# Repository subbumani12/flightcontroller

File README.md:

# Flight Controller

A custom **STM32F411-based flight controller PCB** designed for multirotor, UAV, robotics, and embedded flight-control applications.

The board integrates an IMU, magnetometer, barometric sensor, EEPROM, MicroSD storage, USB-C, SWD debugging, UART interfaces, and dedicated motor/auxiliary outputs on a compact **2-layer PCB** designed in KiCad.

## 3D Render

---

## ✈️ Overview

This project is a custom flight-controller hardware design centered around the **STM32F411RET6 ARM Cortex-M4** microcontroller.

The STM32 handles sensor acquisition, flight-control processing, peripheral communication, data logging, and motor/auxiliary output generation.

The board combines:

* Inertial sensing
* Magnetic heading measurement
* Barometric altitude measurement
* Non-volatile configuration storage
* Flight-data logging
* USB communication
* SWD programming/debugging
* Motor and auxiliary outputs
* UART communication

The PCB was designed in **KiCad**, with emphasis on compact routing, sensor decoupling, accessible debugging, and organized external interfaces.

---

## 🔧 Hardware Features

| Component             | Part                                              |
| --------------------- | ------------------------------------------------- |
| **Microcontroller**   | STM32F411RET6                                     |
| **IMU**               | LSM6DS3 – 3-axis Accelerometer + 3-axis Gyroscope |
| **Magnetometer**      | LIS3MDL – 3-axis                                  |
| **Barometer**         | BMP280                                            |
| **EEPROM**            | AT24C256A                                         |
| **Storage**           | MicroSD                                           |
| **USB**               | USB Type-C                                        |
| **Debug**             | SWD                                               |
| **Serial**            | UART1 / UART2                                     |
| **Motor Outputs**     | MOTOR1 / MOTOR2 / MOTOR3                          |
| **Auxiliary Outputs** | AUX1 / AUX2 / AUX3                                |
| **Logic Supply**      | 3.3 V                                             |
| **PCB**               | 2-layer                                           |
| **EDA Tool**          | KiCad                                             |

The complete hardware feature set is documented in the original design specification.

---

## 🧠 System Architecture

```text
                         USB Type-C
                             │
                             ▼
                       USB Protection
                             │
                             ▼
                       Power / 3.3 V
                             │
                             ▼
                    ┌─────────────────┐
                    │   STM32F411     │
                    │   Flight MCU    │
                    └────────┬────────┘
                             │
          ┌──────────────────┼──────────────────┐
          │                  │                  │
          ▼                  ▼                  ▼
        I²C                 SPI               UART
          │                  │                  │
    ┌─────┼─────┐       ┌────┴────┐       ┌────┴────┐
    ▼     ▼     ▼       ▼         ▼       ▼         ▼
  LSM6DS3 LIS3MDL EEPROM BMP280   MicroSD  UART1    UART2
    │     │
    └─────┴────── Sensor Data
                    │
                    ▼
              STM32 Processing
                    │
             ┌──────┴──────┐
             ▼             ▼
        Motor Outputs   AUX Outputs
             │
             ▼
            ESCs
```

---

## 📡 Sensors & Peripherals

### LSM6DS3 IMU

The **LSM6DS3** provides:

* 3-axis accelerometer
* 3-axis gyroscope

It serves as the primary inertial sensor for attitude estimation, angular-rate measurement, motion detection, and flight-control feedback.

The IMU communicates with the STM32 through **I²C**.

### LIS3MDL Magnetometer

The **LIS3MDL** provides 3-axis magnetic-field measurements and can be used as a magnetic heading reference for navigation and orientation estimation.

It communicates through **I²C** and includes an interrupt connection to the MCU.

### BMP280 Barometer

The **BMP280** provides pressure measurements for:

* Relative altitude estimation
* Altitude-hold applications
* Vertical-motion estimation
* Flight-data logging

The sensor is connected through **SPI**.

### AT24C256A EEPROM

The onboard EEPROM provides non-volatile storage for:

* Configuration parameters
* Calibration data
* Controller settings
* Persistent system information

### MicroSD

A dedicated MicroSD interface provides onboard flight-data storage using SPI:

```text
SD_SPI_MOSI
SD_SPI_MISO
SD_SPI_SCK
SD_CHIPSEL
```

It can be used for sensor measurements, telemetry, debugging information, controller parameters, and flight logs.

---

## 🔌 Interfaces

### Motor Outputs

Three dedicated motor interfaces are provided:

```text
MOTOR1_OUT
MOTOR2_OUT
MOTOR3_OUT
```

Each connector provides:

```text
+5V
GND
SIGNAL
```

The motor-control signals are generated using STM32 timer peripherals and can interface with external ESCs or motor-control hardware.

### Auxiliary Outputs

```text
AUX1_OUT
AUX2_OUT
AUX3_OUT
```

Each provides:

```text
+5V
GND
SIGNAL
```

These can be used for additional actuators or flight-controller peripherals.

### UART

Two serial interfaces are exposed:

```text
UART1_TX
UART1_RX

UART2_TX
UART2_RX
```

Potential applications include GPS, telemetry, radio receivers, external sensors, and configuration interfaces.

### SWD

A dedicated SWD interface is provided for programming and debugging:

```text
SWDIO
SWCLK
3.3V
GND
```

The board also includes test points for convenient hardware debugging.

---

## ⚡ Power Architecture

The board uses an onboard **3.3 V regulation stage** for the STM32 and peripheral electronics.

The power section includes:

* Schottky diode protection
* AMS1117-3.3 regulator
* Input/output filtering capacitors
* Power indicator LED
* Ferrite filtering for the MCU supply

The additional ferrite filtering is intended to reduce high-frequency supply noise around the MCU.

---

## 🖥️ USB & Debugging

The board includes a **USB Type-C interface** providing:

* USB D+
* USB D−
* VBUS
* GND

USB ESD protection is included on the data interface.

The USB connection can be used for firmware development, communication, configuration, debugging, and powering the board during development.

Dedicated **BOOT** and **RESET** buttons are also provided for firmware programming, recovery, and MCU reset.

---

## 🧩 PCB Design

Designed using **KiCad**, the PCB focuses on compact two-layer implementation and practical hardware debugging.

### Design considerations

* Compact 2-layer PCB
* Dedicated ground routing/plane
* Local sensor decoupling
* Short high-speed peripheral connections
* Compact MCU placement
* Accessible SWD interface
* Dedicated motor and auxiliary connectors
* UART connectors
* USB Type-C
* Ferrite-filtered MCU supply
* Separated sensitive sensor circuitry
* Hardware test points
* Perimeter mounting holes

---

## 🔄 Flight-Control Data Flow

```text
        ┌─────────────┐
        │    IMU      │
        │   LSM6DS3   │
        └──────┬──────┘
               │
        ┌──────▼──────┐
        │ Magnetometer│
        │   LIS3MDL   │
        └──────┬──────┘
               │
        ┌──────▼──────┐
        │  Barometer  │
        │    BMP280   │
        └──────┬──────┘
               │
               ▼
        ┌──────────────┐
        │  STM32F411   │
        │    MCU       │
        └──────┬───────┘
               │
        ┌──────┼──────────┐
        ▼      ▼          ▼
     Motors   AUX     Telemetry
        │
        ▼
       ESCs
```

The STM32 acquires sensor data, processes the measurements using flight-control firmware, and generates outputs for connected ESCs, motors, and auxiliary peripherals.

---

## 🛠️ Tools & Technologies

* **KiCad** – Schematic & PCB design
* **STM32F411RET6** – ARM Cortex-M4 MCU
* **STM32 development tools / STM32CubeIDE**
* **I²C**
* **SPI**
* **USART**
* **USB**
* **SWD**

---

## 🚀 Potential Future Improvements

Possible future revisions include:

* Additional motor channels
* CAN / CAN-FD
* GPS connector
* Dedicated telemetry interface
* Battery voltage/current monitoring
* Buzzer interface
* Additional IMU / redundant sensors
* External compass connector
* Barometer isolation
* Improved power-input protection
* Dedicated receiver interface
* Additional test points
* Improved PCB signal integrity

---

## 🎯 Applications

This hardware platform can be explored for:

* Multirotor flight controllers
* UAV development
* Drone flight-control systems
* Autonomous aerial vehicles
* Embedded navigation
* Sensor-fusion experiments
* Flight-data logging
* Robotics
* Embedded control systems
* UAV hardware prototyping

---

## 📌 Project Status

**Hardware:** PCB design completed
**EDA:** KiCad
**Architecture:** STM32F411-based
**PCB:** 2-layer

This project is intended for **educational, research, and UAV hardware-development purposes**.

---

## 📄 License

This project is open-source and intended for educational, research, and UAV hardware-development purposes.

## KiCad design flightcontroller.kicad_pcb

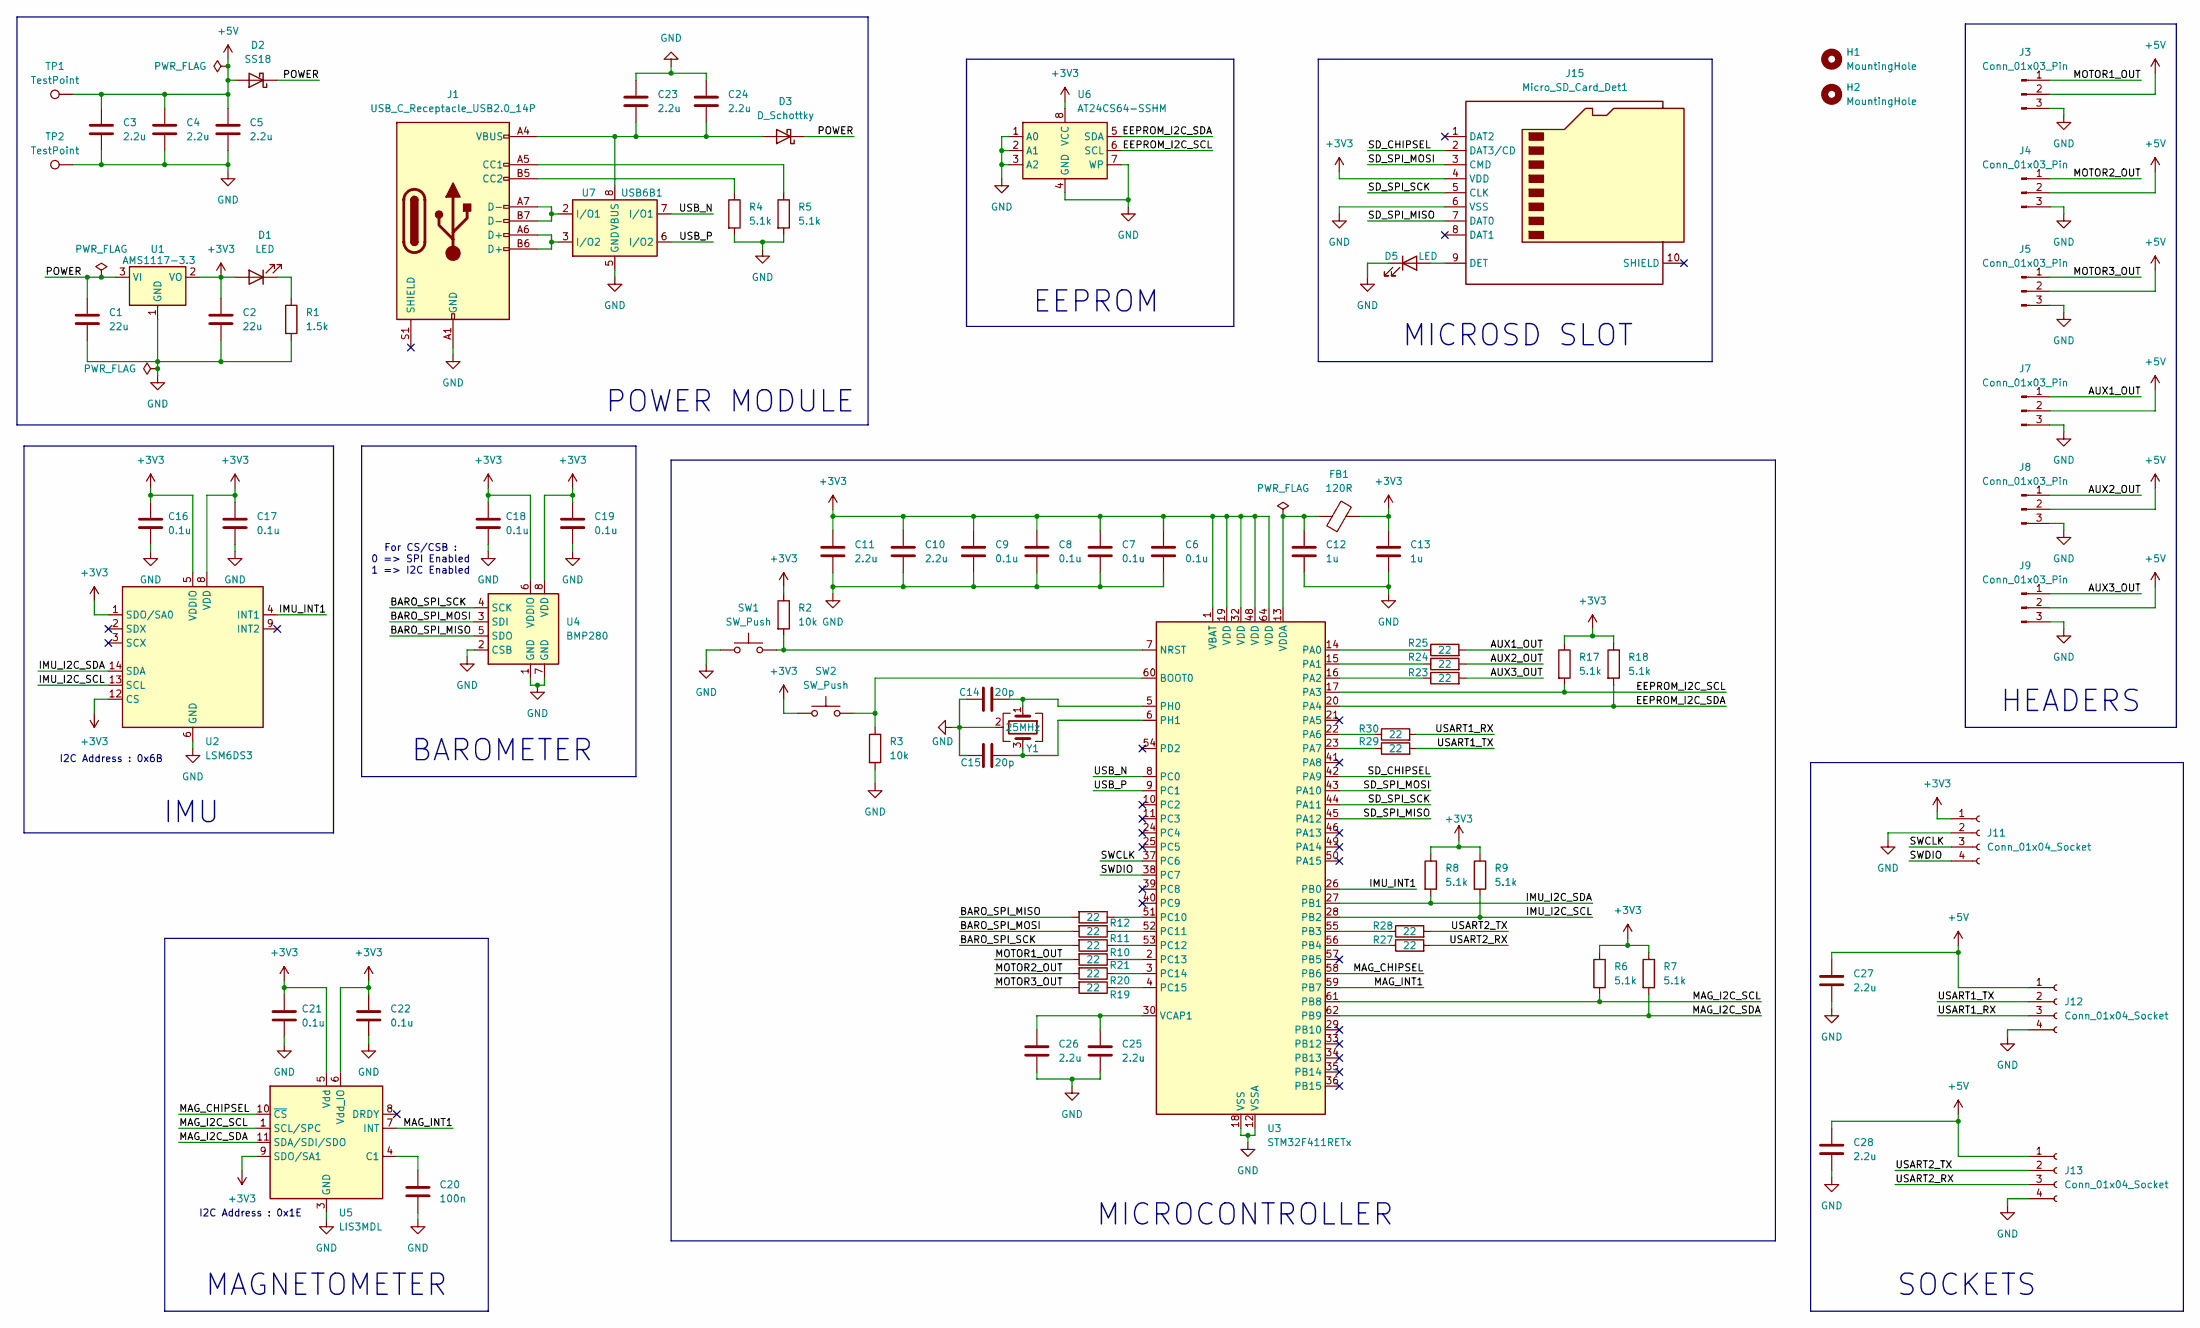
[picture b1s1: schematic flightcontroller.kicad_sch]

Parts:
C1, C2: 22u; C_0402_1005Metric
C3, C4, C5, C10, C11, C23, C24, C25, C26, C27, C28: 2.2u; C_0402_1005Metric
C6, C7, C8, C9, C16, C17, C18, C19, C21, C22: 0.1u; C_0402_1005Metric
C12, C13: 1u; C_0402_1005Metric
C14, C15: 20p; C_0402_1005Metric
C20: 100n; C_0402_1005Metric
D1, D5: LED; LED_0603_1608Metric
D2: SS18; D_SMA
D3: D_Schottky; D_0603_1608Metric
FB1: 120R; L_0805_2012Metric
H1, H2: MountingHole; MountingHole_5mm
J1: USB_C_Receptacle_USB2.0_14P; USB_C_Receptacle_HRO_TYPE-C-31-M-12
J3, J4, J5, J7, J8, J9: Conn_01x03_Pin; PinHeader_1x03_P2.54mm_Vertical
J11, J12, J13: Conn_01x04_Socket; PinSocket_1x04_P2.54mm_Vertical
J15: Micro_SD_Card_Det1; microSD_HC_Molex_104031-0811
R1: 1.5k; R_0402_1005Metric
R2, R3: 10k; R_0402_1005Metric
R4, R5, R6, R7, R8, R9, R17, R18: 5.1k; R_0402_1005Metric
R10, R11, R12, R19, R20, R21, R23, R24, R25, R27, R28, R29, R30: 22; R_0402_1005Metric
SW1, SW2: SW_Push; SW_SPST_TL3305A
TP1, TP2: TestPoint; TestPoint_THTPad_D2.0mm_Drill1.0mm
U1: AMS1117-3.3; SOT-223-3_TabPin2
U2: LSM6DS3; LGA-14_3x2.5mm_P0.5mm_LayoutBorder3x4y
U3: STM32F411RETx; LQFP-64_10x10mm_P0.5mm
U4: BMP280; Bosch_LGA-8_2x2.5mm_P0.65mm_ClockwisePinNumbering
U5: LIS3MDL; LGA-12_2x2mm_P0.5mm
U6: AT24CS64-SSHM; SOIC-8_3.9x4.9mm_P1.27mm
U7: USB6B1; SOIC-8_3.9x4.9mm_P1.27mm
Y1: 25MHz; Crystal_SMD_0603-4Pin_6.0x3.5mm

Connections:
+3V3: C2.1, C6.1, C7.1, C8.1, C9.1, C10.1, C11.1, C13.1, C16.1, C17.1, C18.1, C19.1, C21.1, C22.1, D1.2 (A), FB1.2, J11.1, J15.4 (VDD), R2.1, R6.1, R7.1, R8.1, R9.1, R17.1, R18.1, SW2.1, U1.2 (VO), U2.1 (SDO/SA0), U2.5 (VDDIO), U2.8 (VDD), U2.12 (CS), U3.1 (VBAT), U3.19 (VDD), U3.32 (VDD), U3.48 (VDD), U3.64 (VDD), U4.6 (VDDIO), U4.8 (VDD), U5.5 (Vdd), U5.6 (Vdd_IO), U5.9 (SDO/SA1), U6.8 (VCC)
+5V: C3.1, C4.1, C5.1, C27.1, C28.1, D2.2 (A), J3.2, J4.2, J5.2, J7.2, J8.2, J9.2, J12.1, J13.1, TP1.1
/AUX1_OUT: J7.1, R25.2
/AUX2_OUT: J8.1, R24.2
/AUX3_OUT: J9.1, R23.2
/BARO_SPI_MISO: R12.2, U4.5 (SDO)
/BARO_SPI_MOSI: R11.2, U4.3 (SDI)
/BARO_SPI_SCK: R10.2, U4.4 (SCK)
/EEPROM_I2C_SCL: R17.2, U3.17 (PA3), U6.6 (SCL)
/EEPROM_I2C_SDA: R18.2, U3.20 (PA4), U6.5 (SDA)
/IMU_I2C_SCL: R9.2, U2.13 (SCL), U3.28 (PB2)
/IMU_I2C_SDA: R8.2, U2.14 (SDA), U3.27 (PB1)
/IMU_INT1: U2.4 (INT1), U3.26 (PB0)
/MAG_CHIPSEL: U3.58 (PB6), U5.10 (~CS)
/MAG_I2C_SCL: R6.2, U3.61 (PB8), U5.1 (SCL/SPC)
/MAG_I2C_SDA: R7.2, U3.62 (PB9), U5.11 (SDA/SDI/SDO)
/MAG_INT1: U3.59 (PB7), U5.7 (INT)
/MOTOR1_OUT: J3.1, R21.2
/MOTOR2_OUT: J4.1, R20.2
/MOTOR3_OUT: J5.1, R19.2
/POWER: C1.1, D2.1 (K), D3.1 (K), U1.3 (VI)
/SD_CHIPSEL: J15.2 (DAT3/CD), U3.42 (PA9)
/SD_SPI_MISO: J15.7 (DAT0), U3.45 (PA12)
/SD_SPI_MOSI: J15.3 (CMD), U3.43 (PA10)
/SD_SPI_SCK: J15.5 (CLK), U3.44 (PA11)
/SWCLK: J11.3, U3.37 (PC6)
/SWDIO: J11.4, U3.38 (PC7)
/USART1_RX: J12.3, R30.2
/USART1_TX: J12.2, R29.2
/USART2_RX: J13.3, R27.2
/USART2_TX: J13.2, R28.2
/USB_N: U3.8 (PC0), U7.7 (I/O1)
/USB_P: U3.9 (PC1), U7.6 (I/O2)
GND: C1.2, C2.2, C3.2, C4.2, C5.2, C6.2, C7.2, C8.2, C9.2, C10.2, C11.2, C12.2, C13.2, C14.1, C15.2, C16.2, C17.2, C18.2, C19.2, C20.2, C21.2, C22.2, C23.1, C24.1, C25.2, C26.2, C27.2, C28.2, D5.1 (K), J1.A1 (GND), J1.A12 (GND), J1.B1 (GND), J1.B12 (GND), J3.3, J4.3, J5.3, J7.3, J8.3, J9.3, J11.2, J12.4, J13.4, J15.6 (VSS), R1.2, R3.2, R4.2, R5.2, SW1.1, TP2.1, U1.1 (GND), U2.6 (GND), U2.7 (GND), U3.12 (VSSA), U3.18 (VSS), U3.31 (VSS), U3.47 (VSS), U3.63 (VSS), U4.1 (GND), U4.2 (CSB), U4.7 (GND), U5.2 (GND), U5.3 (GND), U5.12 (GND), U6.1 (A0), U6.2 (A1), U6.3 (A2), U6.4 (GND), U6.7 (WP), U7.4 (GND), U7.5 (GND), Y1.2 (G), Y1.4 (G)
unnamed: D1.1 (K), R1.1
unnamed: C23.2, C24.2, D3.2 (A), J1.A4 (VBUS), J1.A9 (VBUS), J1.B4 (VBUS), J1.B9 (VBUS), U7.1 (VBUS), U7.8 (VBUS)
unnamed: D5.2 (A), J15.9 (DET)
unnamed: J1.A5 (CC1), R5.1
unnamed: J1.B5 (CC2), R4.1
unnamed: J1.A6 (D+), J1.B6 (D+), U7.3 (I/O2)
unnamed: J1.A7 (D-), J1.B7 (D-), U7.2 (I/O1)
unnamed: R3.1, SW2.2, U3.60 (BOOT0)
unnamed: R2.2, SW1.2, U3.7 (NRST)
unnamed: R25.1, U3.14 (PA0)
unnamed: R24.1, U3.15 (PA1)
unnamed: R23.1, U3.16 (PA2)
unnamed: R30.1, U3.22 (PA6)
unnamed: R29.1, U3.23 (PA7)
unnamed: R28.1, U3.55 (PB3)
unnamed: R27.1, U3.56 (PB4)
unnamed: R12.1, U3.51 (PC10)
unnamed: R11.1, U3.52 (PC11)
unnamed: R10.1, U3.53 (PC12)
unnamed: R21.1, U3.2 (PC13)
unnamed: R20.1, U3.3 (PC14)
unnamed: R19.1, U3.4 (PC15)
unnamed: C14.2, U3.5 (PH0), Y1.1
unnamed: C15.1, U3.6 (PH1), Y1.3
unnamed: C25.1, C26.1, U3.30 (VCAP1)
unnamed: C12.1, FB1.1, U3.13 (VDDA)
unnamed: C20.1, U5.4 (C1)

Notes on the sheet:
BAROMETER
For CS/CSB : 0 => SPI Enabled 1 => I2C Enabled
I2C Address : 0x1E
I2C Address : 0x6B
MICROSD SLOT
MICROCONTROLLER
IMU
SOCKETS
EEPROM
POWER MODULE
MAGNETOMETER
HEADERS

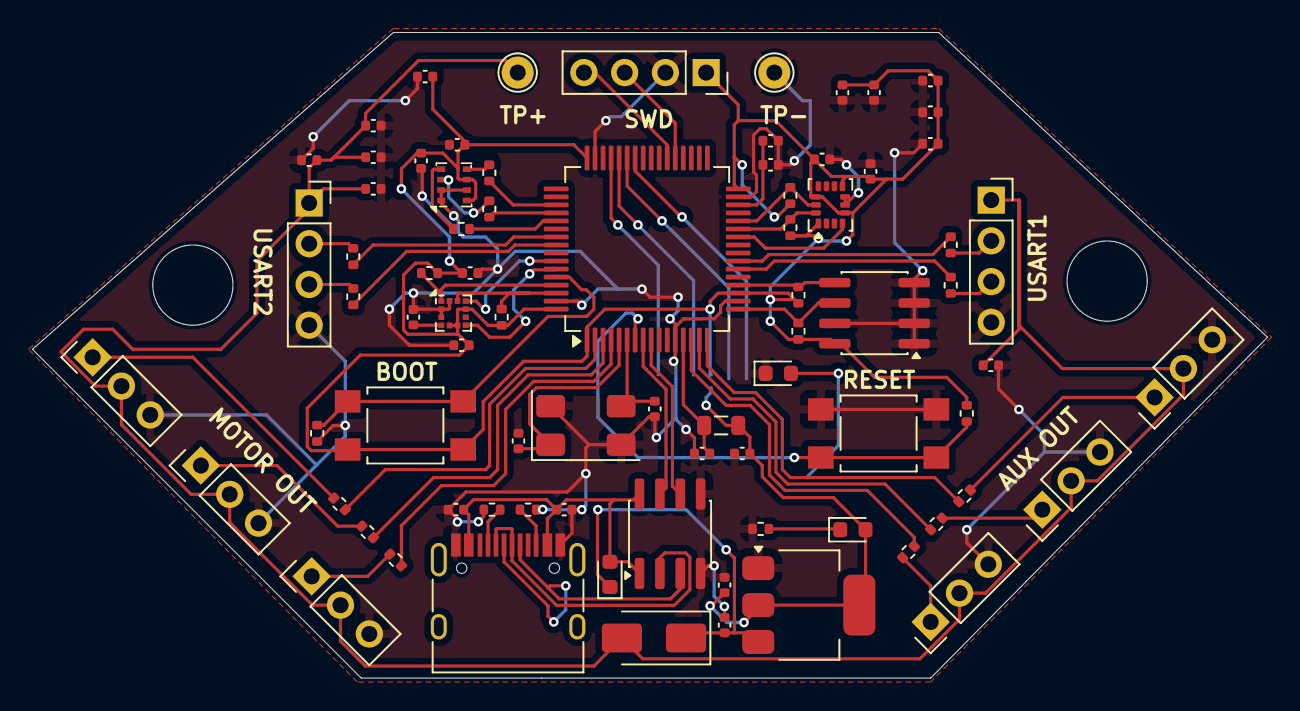
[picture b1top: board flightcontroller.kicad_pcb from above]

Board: 2 copper layers, 77.0 x 40.2 mm, 82 parts (1 on the bottom side), 61 nets.
